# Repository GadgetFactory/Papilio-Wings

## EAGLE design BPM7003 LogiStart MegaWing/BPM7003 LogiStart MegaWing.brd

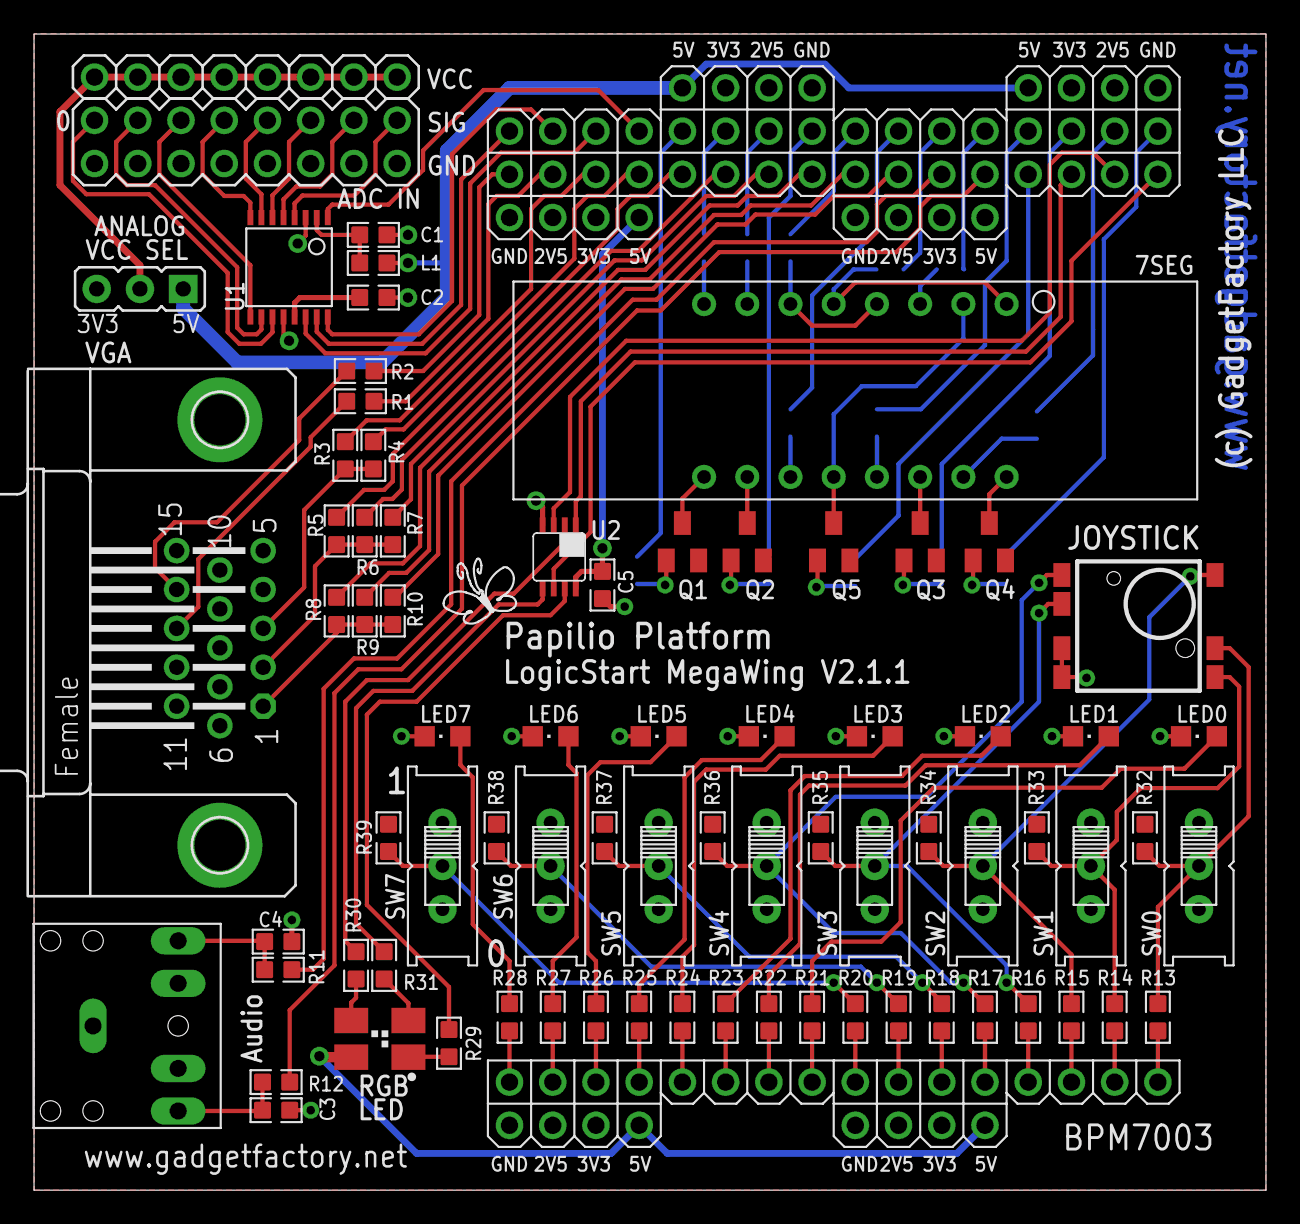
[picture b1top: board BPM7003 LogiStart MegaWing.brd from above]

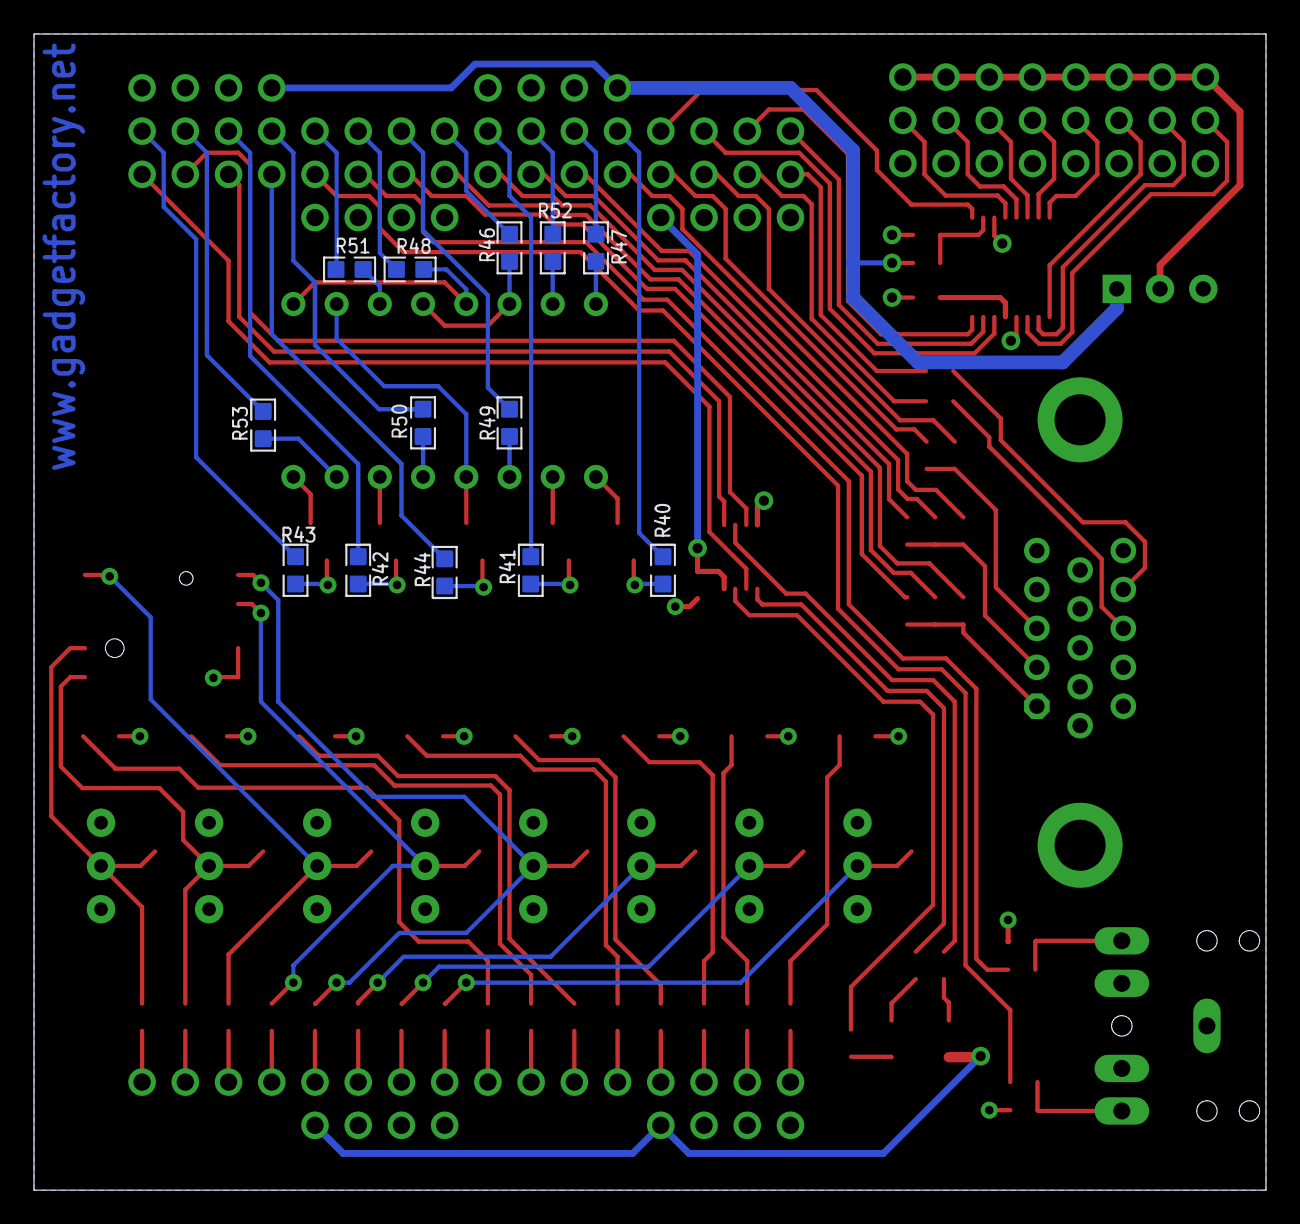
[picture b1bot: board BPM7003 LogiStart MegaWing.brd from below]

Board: 2 copper layers, 72.4 x 67.9 mm, 91 parts (13 on the bottom side), 108 nets.

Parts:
7SEG: 7-SEGMENT-4DIGIT
C1, C2, C5: 0.1uF; 0603
C3, C4: 4.7nF; 0603
J4: AUDIO_JACK_MX295; AUDIOJACK_5PIN_MX295
JOYSTICK: TPA-5POS
JP1: 1X08
JP2: JP2
L1: FERRITEBEAD; 0603
LED0, LED1, LED2, LED3, LED4, LED5, LED6, LED7: CHIPLED_0805
LED8: PLCC4-G
LOGO1: BUTTERFLY_LOGO
Q1, Q2, Q3, Q4, Q5: MMBTA56; SOT23
R1, R2: 82.5E; 0603
R3, R6, R9: 1K; 0603
R4, R7, R10: 499E; 0603
R5, R8: 2K; 0603
R11, R12: 3.3k; 0603
R13, R14, R15, R16, R17, R18, R19, R20, R46, R47, R48, R49, R50, R51, R52, R53: 220E; 0603
R21, R22, R23, R24, R25, R26, R27, R28, R40, R41, R42, R43, R44: 390E; 0603
R29, R31: 180E; 0603
R30: 300E; 0603
R32, R33, R34, R35, R36, R37, R38, R39: 10K; 0603
SV1: MA08-2
SW0, SW1, SW2, SW3, SW4, SW5, SW6, SW7: EG1218
U1: ADC088S102CIMT; TSSOP16
U2: SN74LVC3G07DCT; DCT_R-PDSO-G8
VGA: HDF15H
WING_: MEGAWING_FULL_P1MEGAWING_P1; MEGAWING_FULL_NOHOLES_P1

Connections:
3V3: C2.1, JP2.3, Q1.2, Q2.2, Q3.2, Q4.2, Q5.2, R32.2, R33.2, R34.2, R35.2, R36.2, R37.2, R38.2, R39.2, U1.13, WING_.W2_3V3_2, WING_.W2_3V3_4, WING_.W3_3V3, WING_.W3_3V3_2
5V0: C5.1, JP2.1, L1.2, LED8.2A, U2.8, WING_.W2_5V, WING_.W2_5V_2, WING_.W2_5V_3, WING_.W2_5V_4, WING_.W3_5V, WING_.W3_5V_2
A: 7SEG.12, 7SEG.14, R46.2
AIN0: SV1.16, U1.4
AIN1: SV1.14, U1.5
AIN2: SV1.12, U1.6
AIN3: SV1.10, U1.7
AIN4: SV1.8, U1.8
AIN5: SV1.6, U1.9
AIN6: SV1.4, U1.10
AIN7: SV1.2, U1.11
AN0: Q1.1, R40.2
AN1: Q2.1, R41.2
AN2: Q3.1, R42.2
AN3: Q4.1, R43.2
AN4: Q5.1, R44.1
APOS_A: 7SEG.4, 7SEG.10, Q5.3
AUDIO_L: R11.2, WING_.A27
AUDIO_R: R12.2, WING_.A28
B: 7SEG.16, R47.2
BLUE: R3.2, R4.2, VGA.3
BLUE0: R3.1, WING_.A19
BLUE1: R4.1, WING_.A20
C: 7SEG.9, 7SEG.13, R48.2
D: 7SEG.3, R49.2
DP: 7SEG.7, R53.2
E: 7SEG.5, R50.2
F: 7SEG.11, R51.2
G: 7SEG.15, R52.2
GND: C1.2, C2.2, C3.2, C4.2, C5.2, J4.1, JOYSTICK.1, JOYSTICK.2, LED0.C, LED1.C, LED2.C, LED3.C, LED4.C, LED5.C, LED6.C, LED7.C, SV1.1, SV1.3, SV1.5, SV1.7, SV1.9, SV1.11, SV1.13, SV1.15, SW0.S, SW1.S, SW2.S, SW3.S, SW4.S, SW5.S, SW6.S, SW7.S, U1.3, U1.12, U2.4, VGA.6, VGA.7, VGA.8, VGA.10, VGA.11, WING_.W2_GND, WING_.W2_GND_2, WING_.W2_GND_3, WING_.W2_GND_4, WING_.W3_GND, WING_.W3_GND_2
GREEN: R5.2, R6.2, R7.2, VGA.2
GREEN0: R5.1, WING_.A21
GREEN1: R6.1, WING_.A22
GREEN2: R7.1, WING_.A23
HSYNC: R1.1, WING_.A18
LED0: R21.2, WING_.A40
LED1: R22.2, WING_.A39
LED2: R23.2, WING_.A38
LED3: R24.2, WING_.A37
LED4: R25.2, WING_.A36
LED5: R26.2, WING_.A35
LED6: R27.2, WING_.A34
LED7: R28.2, WING_.A33
LEDB: LED8.3B, R30.2
LEDG: LED8.4G, R31.2
LEDR: LED8.1R, R29.2
unnamed: JP1.1, JP1.2, JP1.3, JP1.4, JP1.5, JP1.6, JP1.7, JP1.8, JP2.2
unnamed: C4.1, J4.3, R11.1
unnamed: C3.1, J4.2, R12.1
unnamed: R41.1, WING_.B24
unnamed: R42.1, WING_.B30
unnamed: R1.2, VGA.13
unnamed: R2.2, VGA.14
unnamed: LED0.A, R21.1
unnamed: LED1.A, R22.1
unnamed: LED2.A, R23.1
unnamed: LED3.A, R24.1
unnamed: LED4.A, R25.1
unnamed: LED5.A, R26.1
unnamed: LED6.A, R27.1
unnamed: LED7.A, R28.1
unnamed: 7SEG.1, Q1.3
unnamed: 7SEG.2, Q2.3
unnamed: 7SEG.6, Q3.3
unnamed: 7SEG.8, Q4.3
unnamed: C1.1, L1.1, U1.2
unnamed: R43.1, WING_.B32
unnamed: R44.2, WING_.A29
unnamed: R40.1, WING_.B21
RED: R8.2, R9.2, R10.2, VGA.1
RED0: R8.1, WING_.A24
RED1: R9.1, WING_.A25
RED2: R10.1, WING_.A26
RGBB: U2.6, WING_.A32
RGBB_OUT: R30.1, U2.2
RGBG: U2.3, WING_.A31
RGBG_OUT: R31.1, U2.5
RGBR: U2.1, WING_.A30
RGBR_OUT: R29.1, U2.7
SEGA: R46.1, WING_.B25
SEGB: R47.1, WING_.B22
SEGC: R48.1, WING_.B27
SEGD: R49.1, WING_.B26
SEGDP: R53.1, WING_.B31
SEGE: R50.1, WING_.B29
SEGF: R51.1, WING_.B28
SEGG: R52.1, WING_.B23
SPI_CS: U1.1, WING_.B20
SPI_DIN: U1.14, WING_.B19
SPI_DOUT: U1.15, WING_.B17
SPI_SCLK: U1.16, WING_.B18
SW0: R13.1, WING_.A48
SW0_JOY_UP_IN: JOYSTICK.3, R13.2, R32.1, SW0.P
SW1: R14.1, WING_.A47
SW1__JOY_DOWN_IN: JOYSTICK.4, R14.2, R33.1, SW1.P
SW2: R15.1, WING_.A46
SW2_JOY_SELECT_IN: JOYSTICK.5, R15.2, R34.1, SW2.P
SW3: R16.1, WING_.A45
SW3_JOY_RIGHT_IN: JOYSTICK.6, R16.2, R35.1, SW3.P
SW4: R17.1, WING_.A44
SW4_JOY_LEFT_IN: JOYSTICK.7, R17.2, R36.1, SW4.P
SW5: R18.1, WING_.A43
SW5_IN: R18.2, R37.1, SW5.P
SW6: R19.1, WING_.A42
SW6_IN: R19.2, R38.1, SW6.P
SW7: R20.1, WING_.A41
SW7_IN: R20.2, R39.1, SW7.P
VSYNC: R2.1, WING_.A17
